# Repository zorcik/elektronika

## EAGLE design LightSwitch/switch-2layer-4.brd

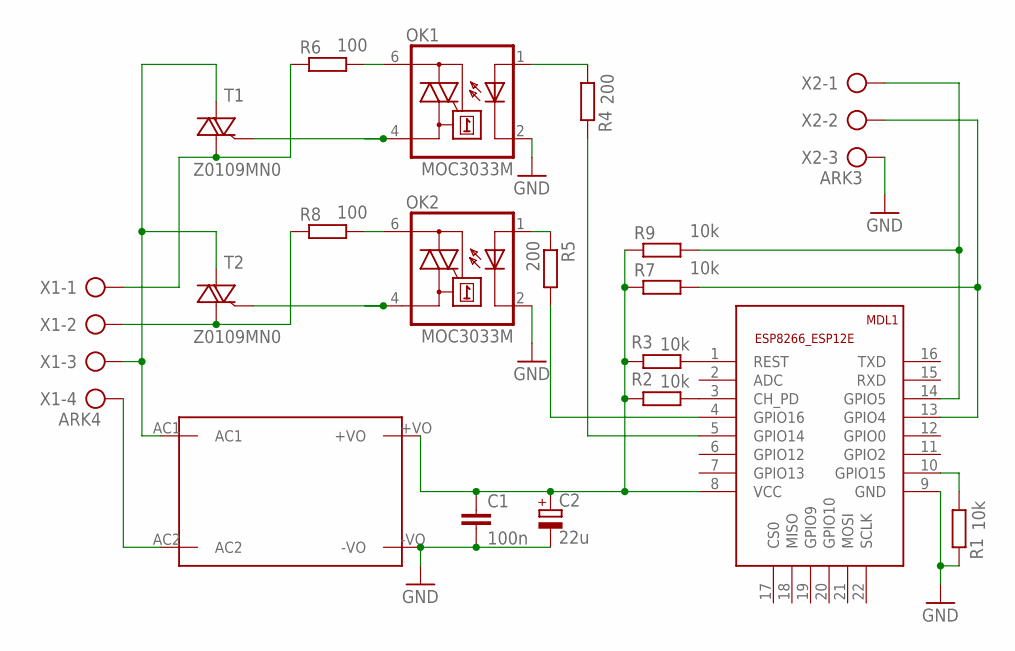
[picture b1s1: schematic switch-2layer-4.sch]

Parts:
C1: 100n; C1206
C2: 22u; E2,5-6
MDL1: ESP12-F; ESP8266-ESP12E
OK1, OK2: MOC3033M; DIL06
R1, R2, R3, R7, R9: 10k; R1206
R4, R5: 200; R1206
R6, R8: 100; R1206
T1, T2: Z0109MN0; SOT223
U$1: HLK-PM03
X1: ARK4; AK500/4
X2: ARK3; AK500/3

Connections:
GND: C1.2, C2.-, MDL1.9 (GND), OK1.2 (C), OK2.2 (C), R1.2, U$1.-VO, X2.3
unnamed: MDL1.10 (GPIO15), R1.1
unnamed: MDL1.1 (REST), R3.1
unnamed: MDL1.3 (CH_PD), R2.1
unnamed: C1.1, C2.+, MDL1.8 (VCC), R2.2, R3.2, R7.1, R9.1, U$1.+VO
unnamed: OK1.6 (A2), R6.2
unnamed: OK2.6 (A2), R8.2
unnamed: OK2.1 (A), R5.1
unnamed: OK1.1 (A), R4.1
unnamed: MDL1.4 (GPIO16), R5.2
unnamed: MDL1.5 (GPIO14), R4.2
unnamed: OK1.4 (A1), T1.3 (G)
unnamed: R8.1, T2.2 (CM), T2.4 (CM), X1.2
unnamed: OK2.4 (A1), T2.3 (G)
unnamed: U$1.AC2, X1.4
unnamed: T1.1 (LD), T2.1 (LD), U$1.AC1, X1.3
unnamed: MDL1.14 (GPIO5), R9.2, X2.1
unnamed: MDL1.13 (GPIO4), R7.2, X2.2
unnamed: R6.1, T1.2 (CM), T1.4 (CM), X1.1

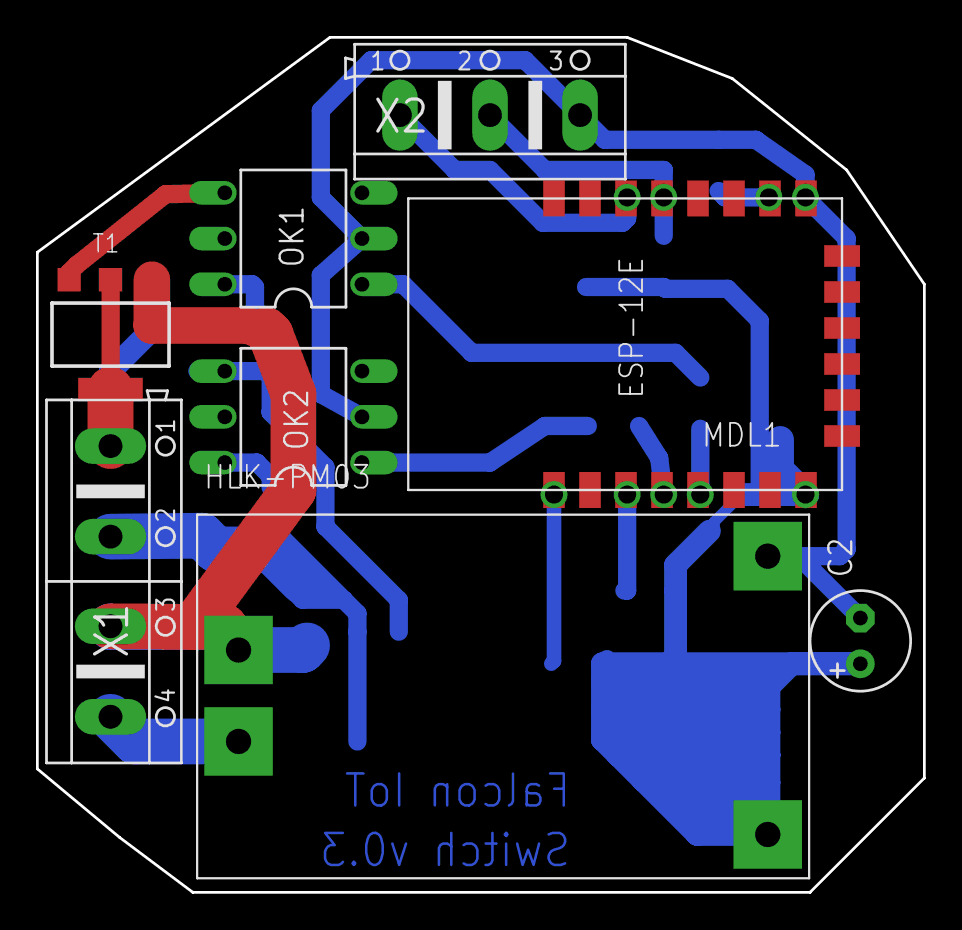
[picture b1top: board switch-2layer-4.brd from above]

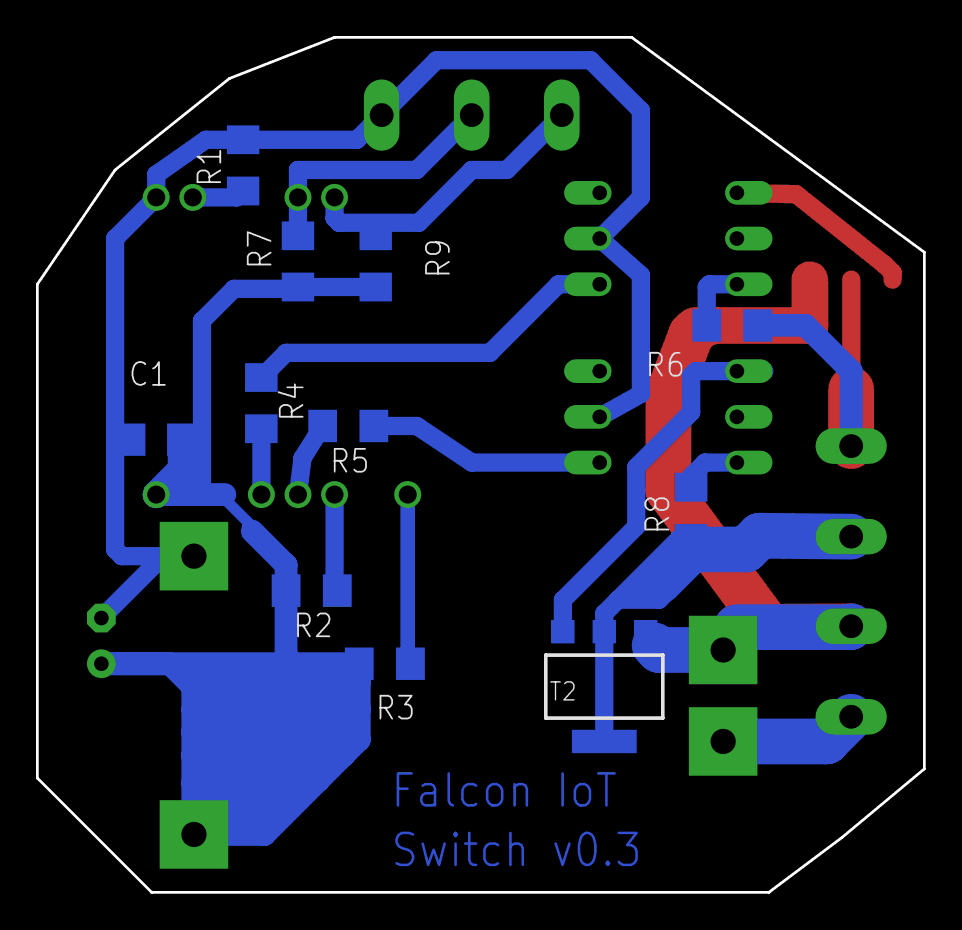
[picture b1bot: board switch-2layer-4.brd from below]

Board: 2 copper layers, 49.3 x 47.5 mm, 19 parts (11 on the bottom side), 19 nets.

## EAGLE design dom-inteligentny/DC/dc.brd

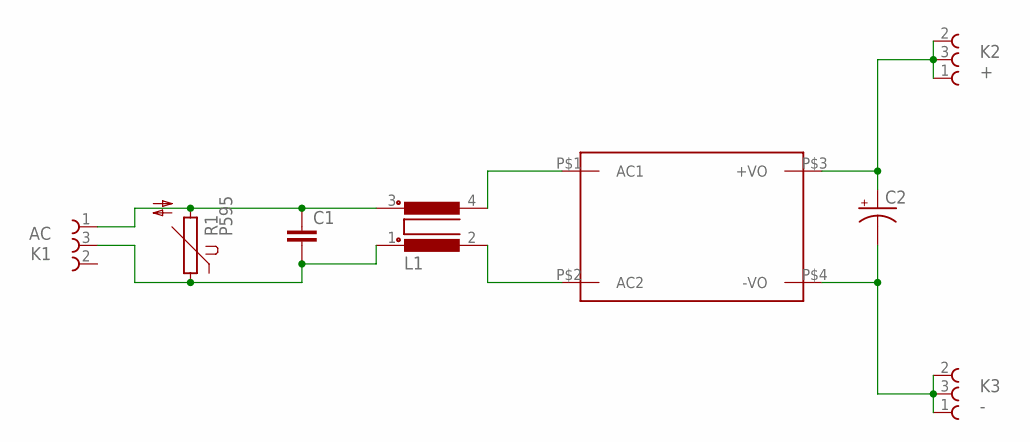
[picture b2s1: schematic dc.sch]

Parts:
C1: C15/7; C15B7
C2: CPOL-USE10-20; EB20D
K1: AC; 691218410003
K2: +; 691218410003
K3: -; 691218410003
L1: R1003UB5; B5
R1: P595
U$1: HLK-PM03HLK-20M; HLK-20M

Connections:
unnamed: C1.1, K1.1 (3), L1.3, R1.2
unnamed: L1.4, U$1.P$1 (AC1)
unnamed: L1.2, U$1.P$2 (AC2)
unnamed: C1.2, K1.3 (2), L1.1, R1.1
unnamed: C2.+, K2.1 (3), K2.2 (1), K2.3 (2), U$1.P$3 (+VO)
unnamed: C2.-, K3.1 (3), K3.2 (1), K3.3 (2), U$1.P$4 (-VO)

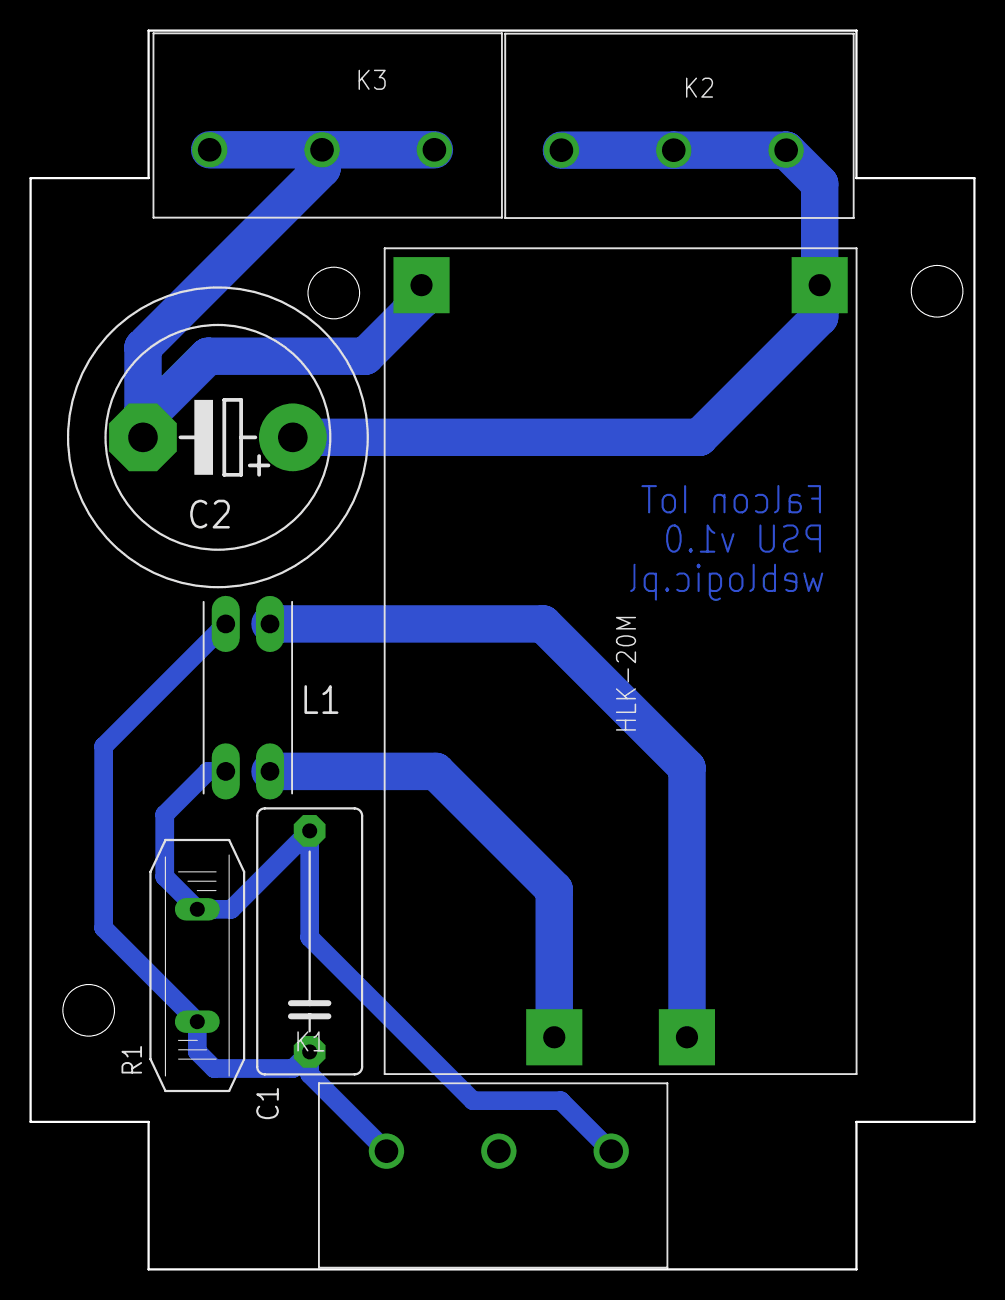
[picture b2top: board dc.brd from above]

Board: 2 copper layers, 64.0 x 84.0 mm, 8 parts (0 on the bottom side), 6 nets.

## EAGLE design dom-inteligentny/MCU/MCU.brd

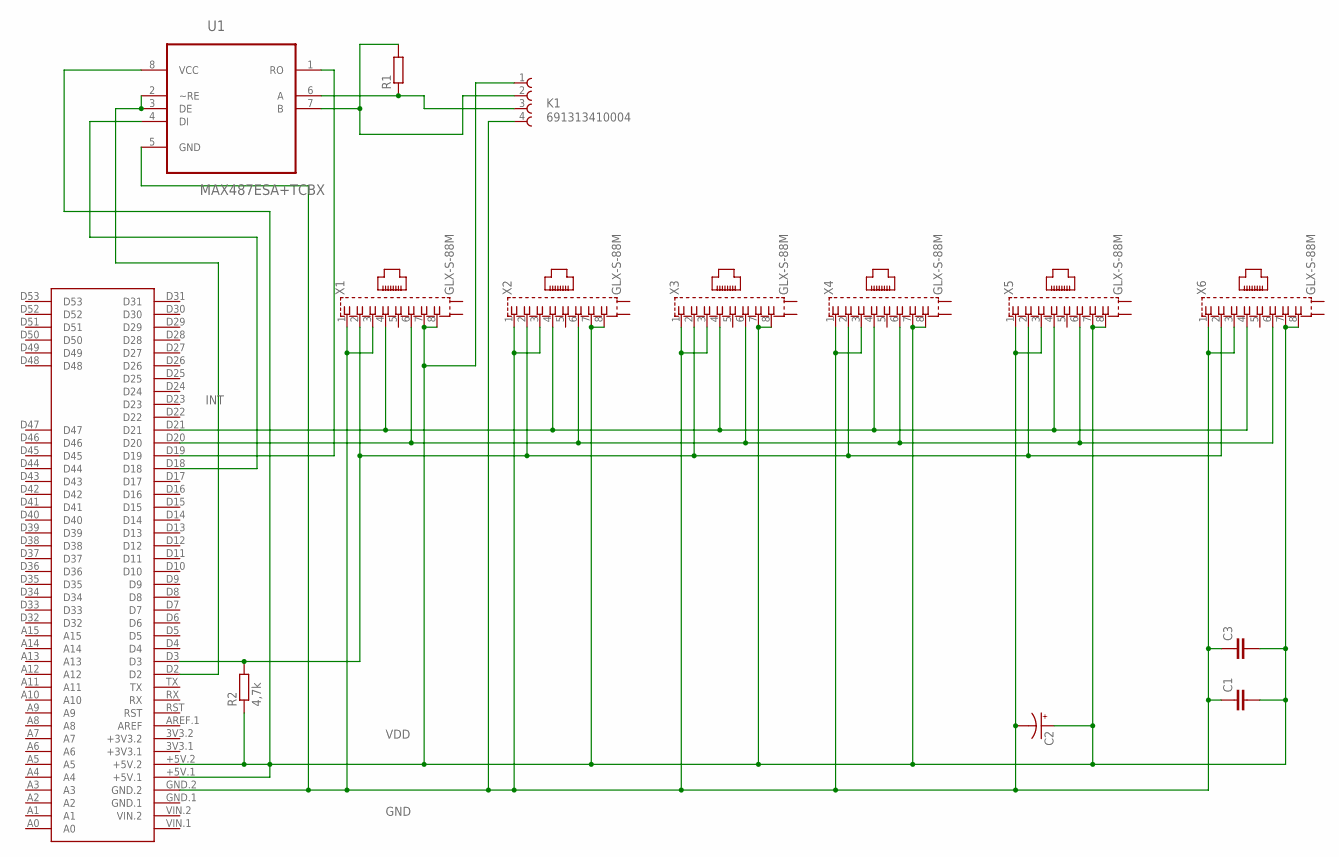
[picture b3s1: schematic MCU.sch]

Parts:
C1, C3: CC1206; C1206
C2: CPOL-US153CLV-0807; 153CLV-0807
K1: 691313410004
R1: RR1206; R1206
R2: 4,7k; R1206
U1: MAX487ESA+TCBX; SOIC127P600X175-8N
U$1: MEGA2560_MIKRO
X1, X2, X3, X4, X5, X6: GLX-S-88M

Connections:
GND: C1.1, C2.-, C3.1, K1.4, U1.5 (GND), U$1.GND.2, X1.1, X1.3, X2.1, X2.3, X3.1, X3.3, X4.1, X4.3, X5.1, X5.3, X6.1, X6.3
INT: R2.2, U$1.D3, X1.2, X2.2, X3.2, X4.2, X5.2, X6.2
unnamed: U1.4 (DI), U$1.D18
unnamed: U1.1 (RO), U$1.D19
unnamed: U1.2 (~RE), U1.3 (DE), U$1.D2
unnamed: K1.3, R1.1, U1.6 (A)
unnamed: K1.2, R1.2, U1.7 (B)
unnamed: U$1.D20, X1.6, X2.6, X3.6, X4.6, X5.6, X6.6
unnamed: U$1.D21, X1.4, X2.4, X3.4, X4.4, X5.4, X6.4
VDD: C1.2, C2.+, C3.2, K1.1, R2.1, U1.8 (VCC), U$1.+5V.1, U$1.+5V.2, X1.7, X1.8, X2.7, X2.8, X3.7, X3.8, X4.7, X4.8, X5.7, X5.8, X6.7, X6.8

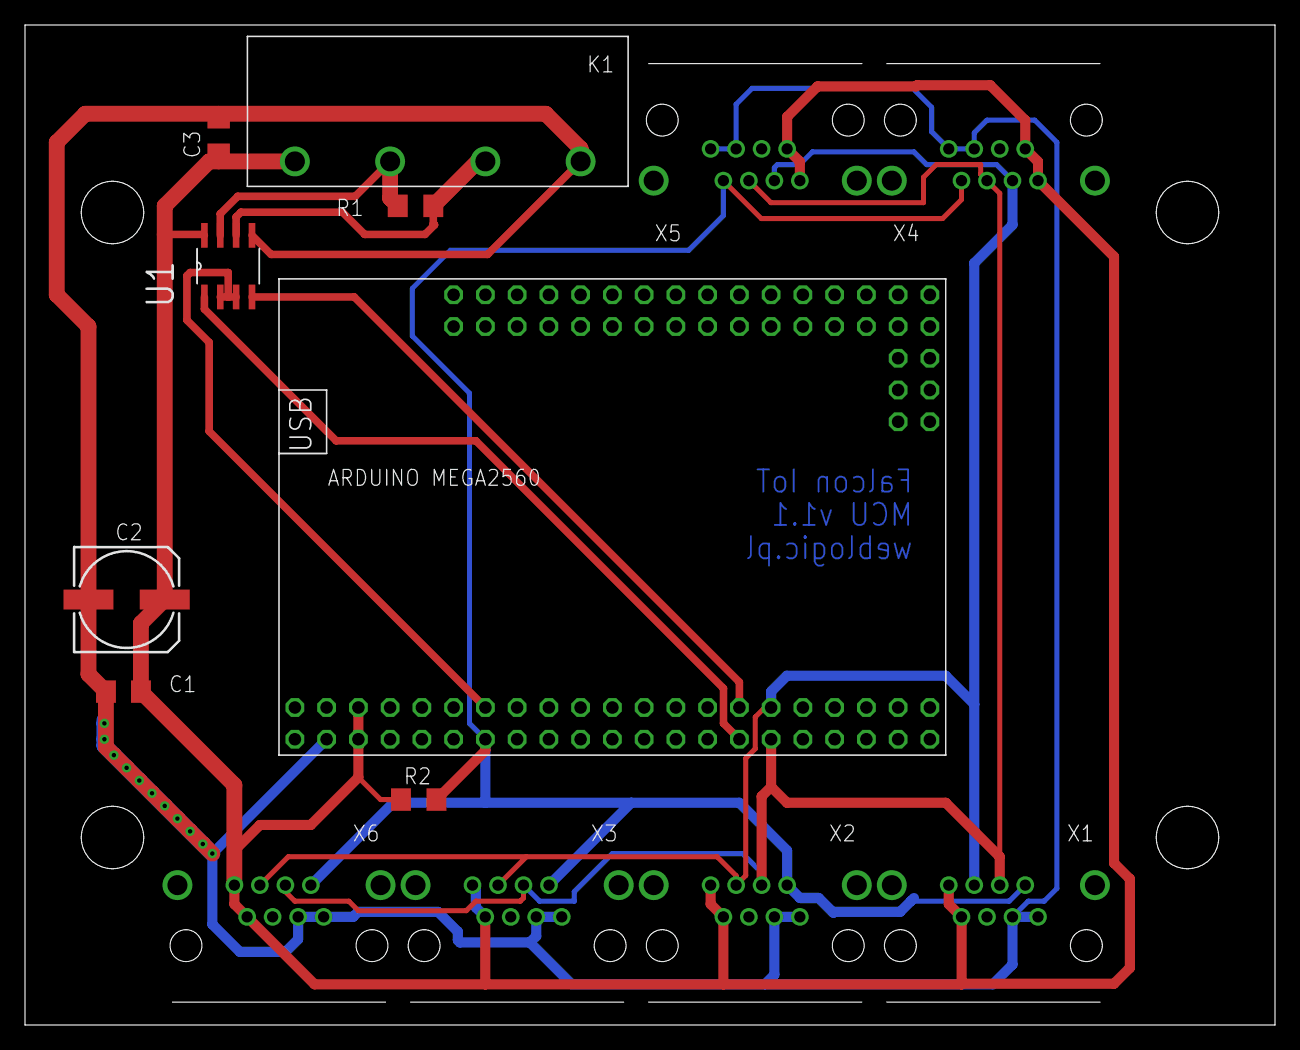
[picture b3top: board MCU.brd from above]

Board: 2 copper layers, 100.0 x 80.0 mm, 14 parts (0 on the bottom side), 10 nets.

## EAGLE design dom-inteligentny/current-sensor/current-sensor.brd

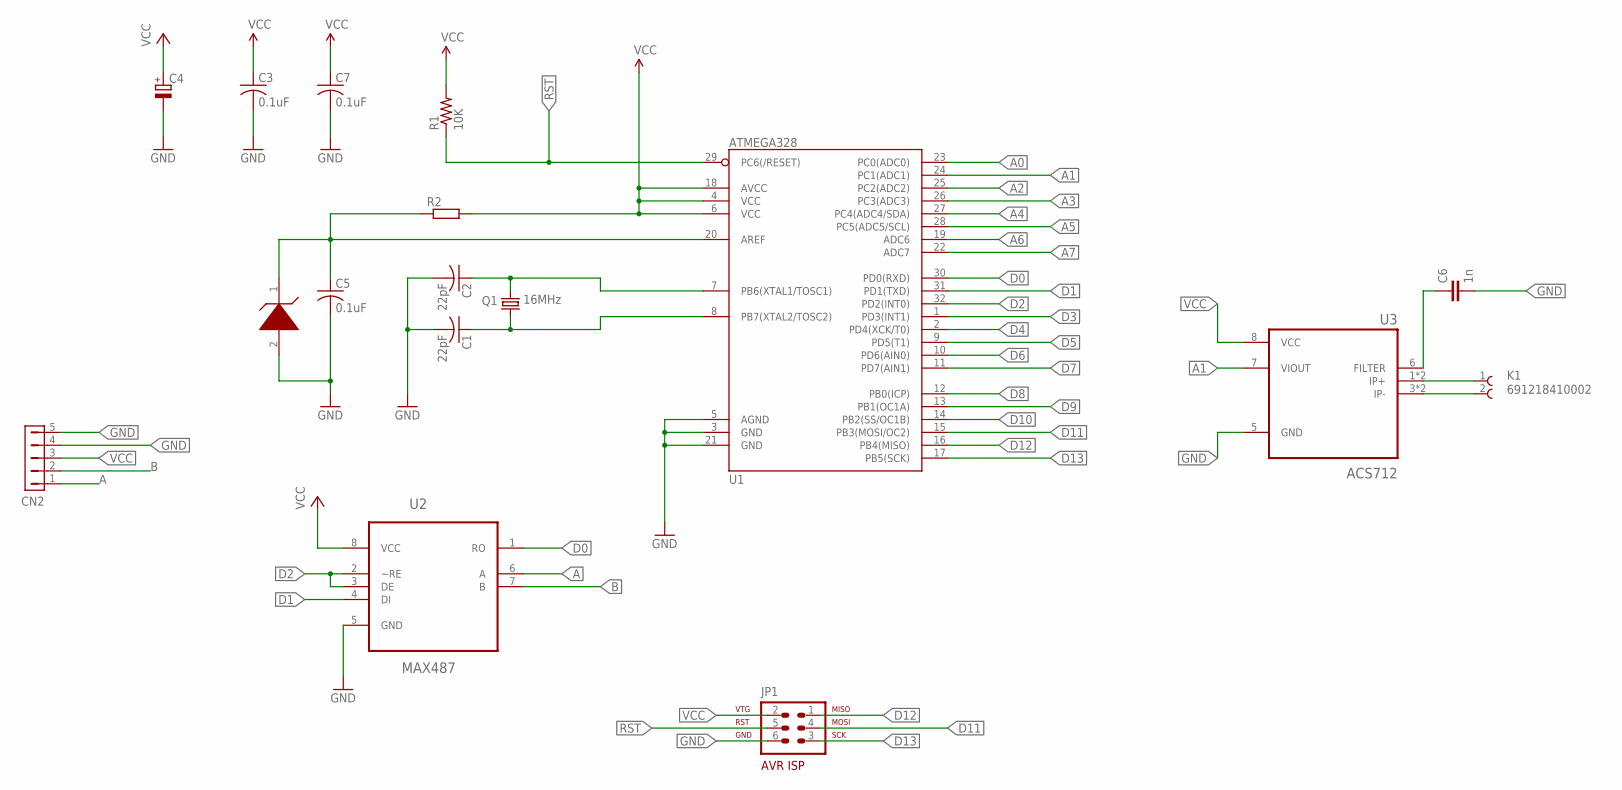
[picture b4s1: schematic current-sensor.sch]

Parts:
C1, C2: 22pF; C1206
C3, C5, C7: 0.1uF; C0805
C4: CPOL-EUSANYO_SMD_C6; SANYO-OSCON_SMD_C6
C6: 1n; C1206
CN2: HDR-1X5-SIP-100; SIP-100-5V
JP1: AVR-ISP-6
K1: 691218410002
Q1: 16MHz; HC49/S
R1: 10K; R1206
R2: RR1206; R1206
U1: ATMEGA328; TQFP32-08
U2: MAX487; SOIC127P600X175-8N
U3: ACS712; SOIC127P600X175-8N
U$1: LM4040; SOT23

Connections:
A: CN2.1, U2.6 (A)
A0: U1.23 (PC0(ADC0))
A1: U1.24 (PC1(ADC1)), U3.7 (VIOUT)
A2: U1.25 (PC2(ADC2))
A3: U1.26 (PC3(ADC3))
A4: U1.27 (PC4(ADC4/SDA))
A5: U1.28 (PC5(ADC5/SCL))
A6: U1.19 (ADC6)
A7: U1.22 (ADC7)
AREF: C5.1, R2.1, U1.20 (AREF), U$1.1 (CATHODE)
B: CN2.2, U2.7 (B)
D0: U1.30 (PD0(RXD)), U2.1 (RO)
D1: U1.31 (PD1(TXD)), U2.4 (DI)
D2: U1.32 (PD2(INT0)), U2.2 (~RE), U2.3 (DE)
D3: U1.1 (PD3(INT1))
D4: U1.2 (PD4(XCK/T0))
D5: U1.9 (PD5(T1))
D6: U1.10 (PD6(AIN0))
D7: U1.11 (PD7(AIN1))
D8: U1.12 (PB0(ICP))
D9: U1.13 (PB1(OC1A))
D10: U1.14 (PB2(SS/OC1B))
D11: JP1.4, U1.15 (PB3(MOSI/OC2))
D12: JP1.1, U1.16 (PB4(MISO))
D13: JP1.3, U1.17 (PB5(SCK))
GND: C1.2, C2.2, C3.2, C4.-, C5.2, C6.2, C7.2, CN2.4, CN2.5, JP1.6, U1.3 (GND), U1.5 (AGND), U1.21 (GND), U2.5 (GND), U3.5 (GND), U$1.2 (ANODE)
unnamed: K1.1, U3.1 (IP+), U3.2 (IP+)
unnamed: K1.2, U3.3 (IP-), U3.4 (IP-)
unnamed: C6.1, U3.6 (FILTER)
unnamed: C2.1, Q1.2, U1.7 (PB6(XTAL1/TOSC1))
unnamed: C1.1, Q1.1, U1.8 (PB7(XTAL2/TOSC2))
RST: JP1.5, R1.1, U1.29 (PC6(/RESET))
VCC: C3.1, C4.+, C7.1, CN2.3, JP1.2, R1.2, R2.2, U1.4 (VCC), U1.6 (VCC), U1.18 (AVCC), U2.8 (VCC), U3.8 (VCC)

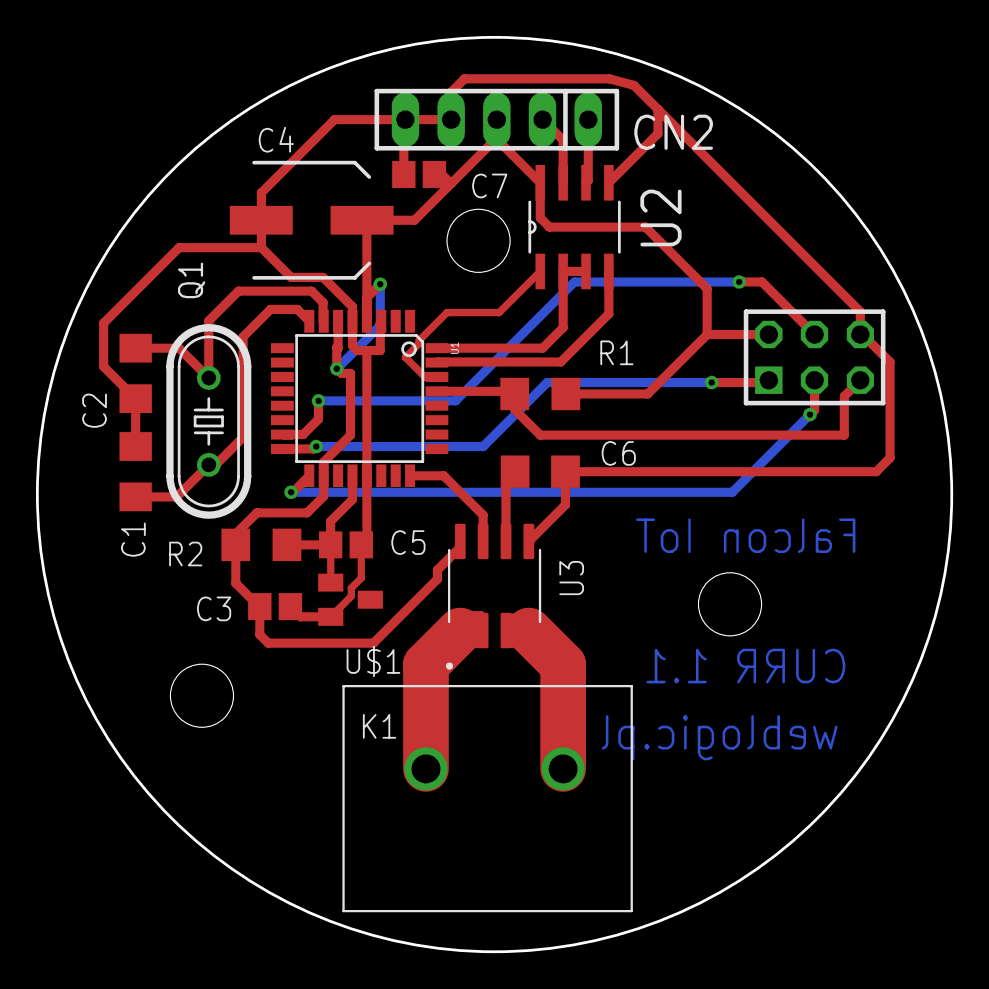
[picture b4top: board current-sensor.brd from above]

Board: 2 copper layers, 50.8 x 50.8 mm, 17 parts (0 on the bottom side), 18 nets.

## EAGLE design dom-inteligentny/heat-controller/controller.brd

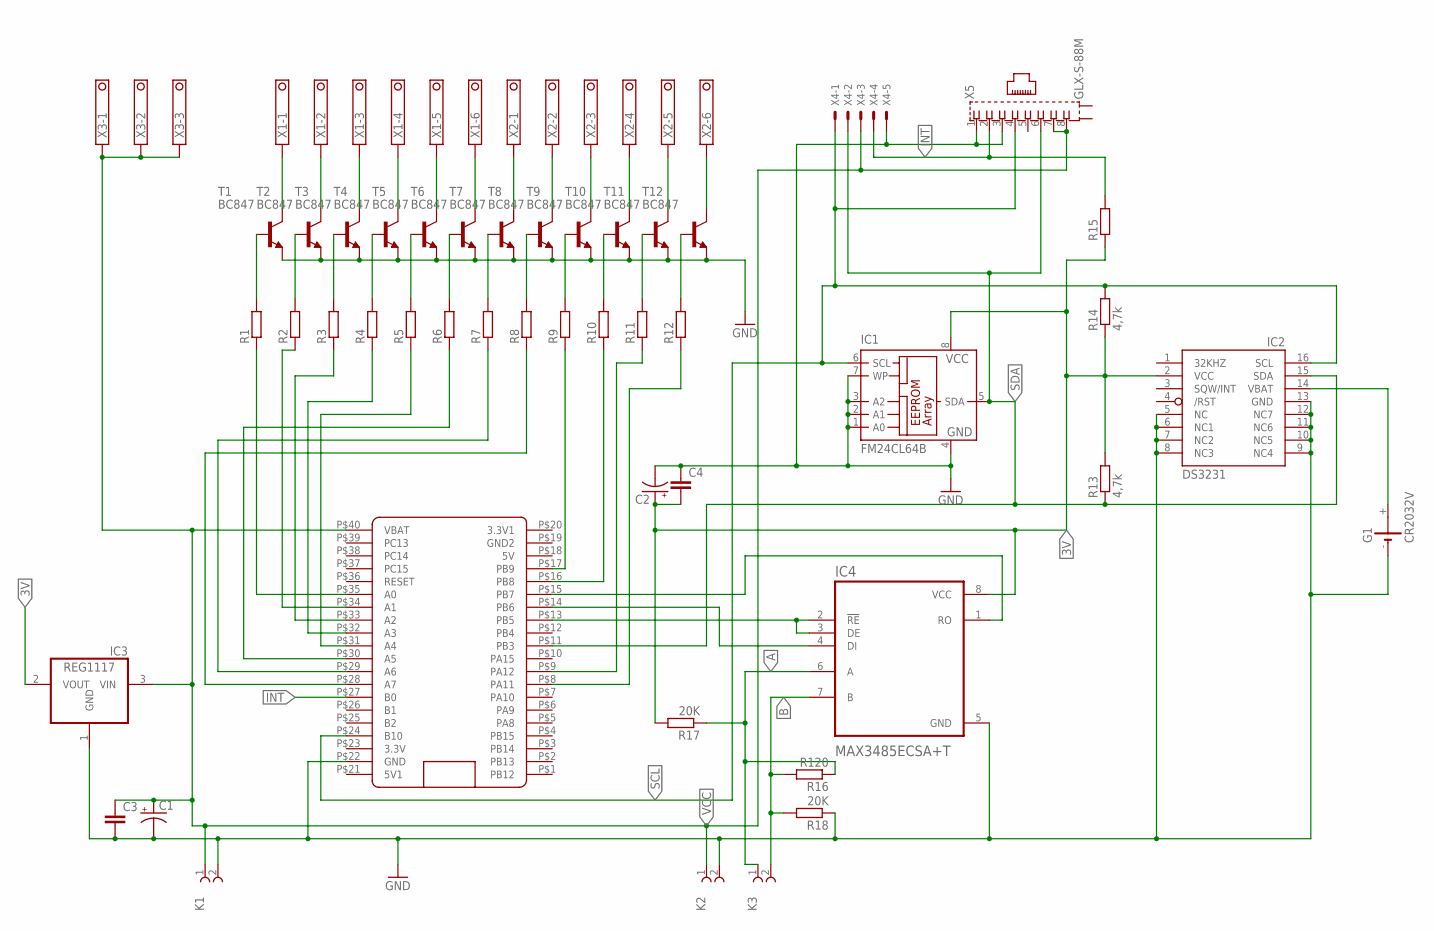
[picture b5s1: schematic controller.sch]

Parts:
C1, C2: CPOL-US153CLV-0810; 153CLV-0810
C3, C4: C; C0805
G1: CR2032V
IC1: FM24CL64B; SO-08M
IC2: DS3231; SO16W
IC3: REG1117; SOT223
IC4: MAX3485ECSA+T; SOIC127P600X175-8N
K1, K2, K3: 691218410002
R1, R2, R3, R4, R5, R6, R7, R8, R9, R10, R11, R12, R15: RR1206; R1206
R13, R14: 4,7k; R1206
R16: R120; R1206
R17, R18: 20K; R1206
T1, T2, T3, T4, T5, T6, T7, T8, T9, T10, T11, T12: BC847; SOT23
U$1: BLACK_STM32F411; BLACK_PILL
X1, X2: TERMINAL-BLOCK-3.5MM-6-PIN-LONG-PAD; TERMINAL-BLOCK-6-PIN-3.5MM-LONG-PAD
X3: TERMINAL-BLOCK-3.5MM-3-PIN-LONG-PAD; TERMINAL-BLOCK-3-PIN-3.5MM-LONG-PAD
X4: JST-XH-05-PIN-LONG-PAD; JST-XH-05-PACKAGE-LONG-PAD
X5: GLX-S-88M

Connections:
3V: C2.+, C4.2, IC1.8 (VCC), IC2.2 (VCC), IC3.2 (VOUT), IC4.8 (VCC), R13.2, R14.1, R15.1, R17.2
5V1: U$1.P$21 (5V1)
A: IC4.6 (A), K3.1, R16.1, R17.1
B: IC4.7 (B), K3.2, R16.2, R18.2
GND: C1.-, C2.-, C3.2, C4.1, G1.-, IC1.1 (A0), IC1.2 (A1), IC1.3 (A2), IC1.4 (GND), IC1.7 (WP), IC2.5 (NC), IC2.6 (NC1), IC2.7 (NC2), IC2.8 (NC3), IC2.9 (NC4), IC2.10 (NC5), IC2.11 (NC6), IC2.12 (NC7), IC2.13 (GND), IC3.1 (GND), IC4.5 (GND), K1.2, K2.2, R18.1, T1.2 (E), T2.2 (E), T3.2 (E), T4.2 (E), T5.2 (E), T6.2 (E), T7.2 (E), T8.2 (E), T9.2 (E), T10.2 (E), T11.2 (E), T12.2 (E), U$1.P$22 (GND), X4.5, X5.1, X5.3
INT: R15.2, U$1.P$27 (B0), X4.4, X5.2
unnamed: G1.+, IC2.14 (VBAT)
unnamed: IC4.2 (!RE), IC4.3 (DE), U$1.P$13 (PB5)
unnamed: IC4.4 (DI), U$1.P$14 (PB6)
unnamed: IC4.1 (RO), U$1.P$15 (PB7)
unnamed: R1.1, U$1.P$35 (A0)
unnamed: R2.1, U$1.P$34 (A1)
unnamed: R3.1, U$1.P$33 (A2)
unnamed: R4.1, U$1.P$32 (A3)
unnamed: R5.1, U$1.P$31 (A4)
unnamed: R6.1, U$1.P$30 (A5)
unnamed: R7.1, U$1.P$29 (A6)
unnamed: R8.1, U$1.P$28 (A7)
unnamed: R9.1, U$1.P$17 (PB9)
unnamed: R10.1, U$1.P$16 (PB8)
unnamed: R11.1, U$1.P$9 (PA12)
unnamed: R12.1, U$1.P$8 (PA11)
unnamed: R1.2, T1.1 (B)
unnamed: R2.2, T2.1 (B)
unnamed: R3.2, T3.1 (B)
unnamed: R4.2, T4.1 (B)
unnamed: R5.2, T5.1 (B)
unnamed: R6.2, T6.1 (B)
unnamed: R7.2, T7.1 (B)
unnamed: R8.2, T8.1 (B)
unnamed: R9.2, T9.1 (B)
unnamed: R10.2, T10.1 (B)
unnamed: R11.2, T11.1 (B)
unnamed: R12.2, T12.1 (B)
unnamed: T1.3 (C), X1.1
unnamed: T2.3 (C), X1.2
unnamed: T3.3 (C), X1.3
unnamed: T4.3 (C), X1.4
unnamed: T5.3 (C), X1.5
unnamed: T6.3 (C), X1.6
unnamed: T7.3 (C), X2.1
unnamed: T8.3 (C), X2.2
unnamed: T9.3 (C), X2.3
unnamed: T10.3 (C), X2.4
unnamed: T11.3 (C), X2.5
unnamed: T12.3 (C), X2.6
SCL: IC1.6 (SCL), IC2.16 (SCL), R14.2, U$1.P$24 (B10), X4.1, X5.4
SDA: IC1.5 (SDA), IC2.15 (SDA), R13.1, U$1.P$11 (PB3), X4.2, X5.6
VCC: C1.+, C3.1, IC3.3 (VIN), K1.1, K2.1, U$1.P$40 (VBAT), X3.1, X3.2, X3.3, X4.3, X5.7, X5.8

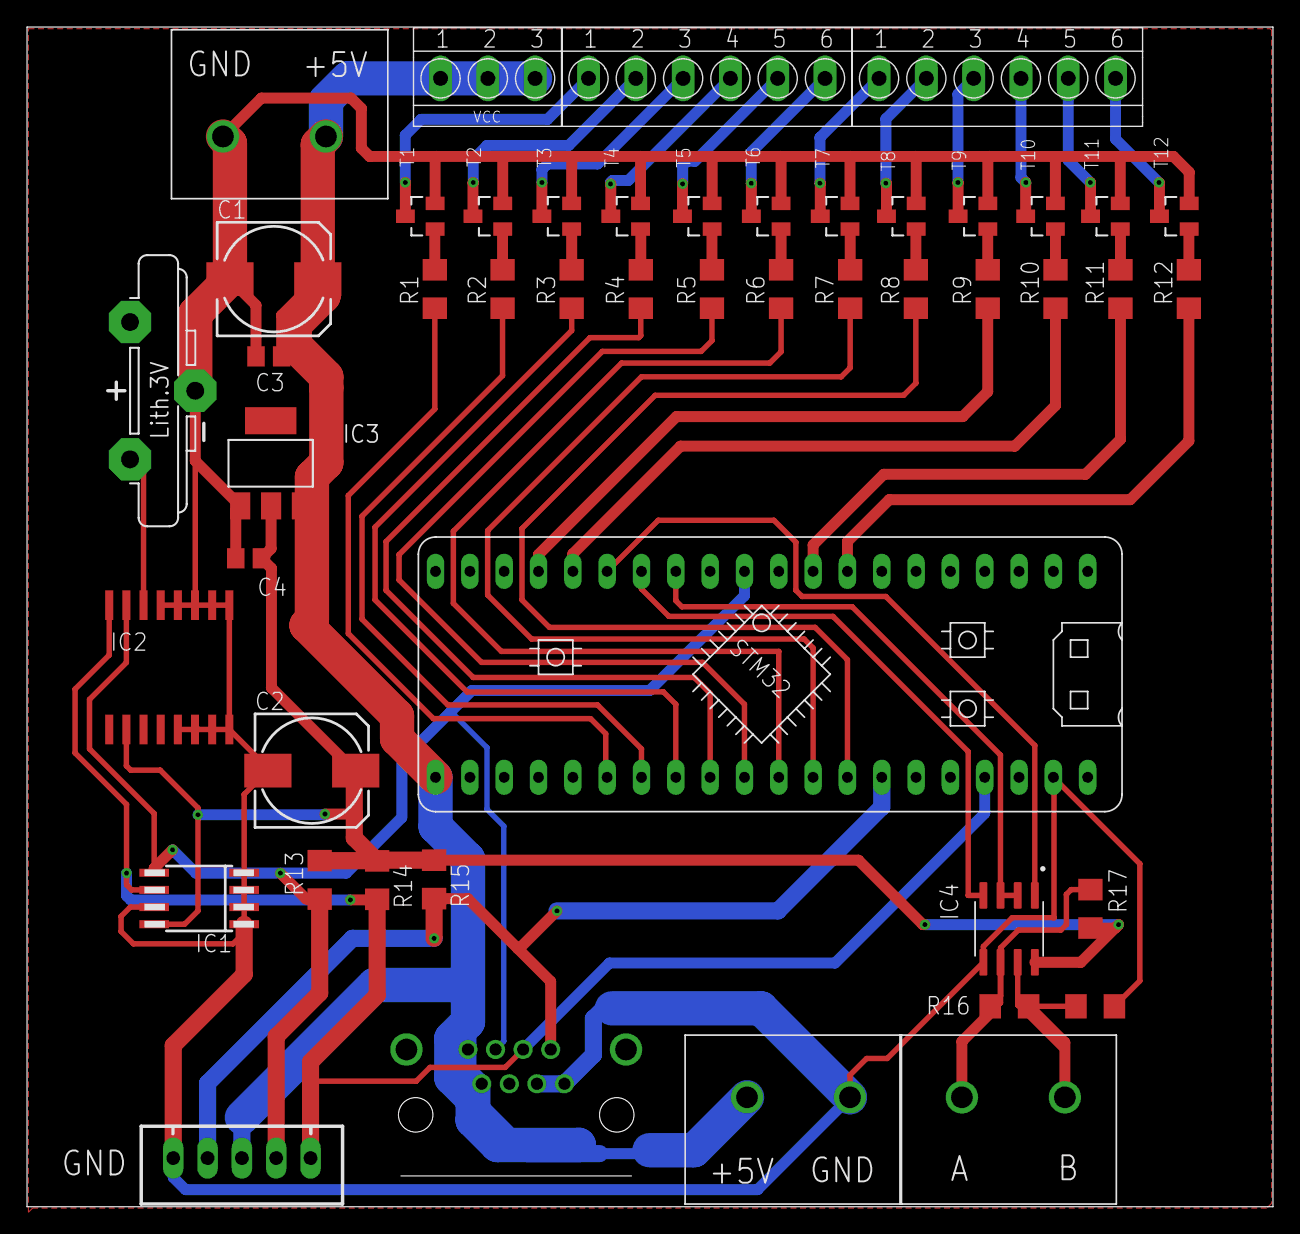
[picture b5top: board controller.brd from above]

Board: 2 copper layers, 92.2 x 87.3 mm, 48 parts (0 on the bottom side), 48 nets.

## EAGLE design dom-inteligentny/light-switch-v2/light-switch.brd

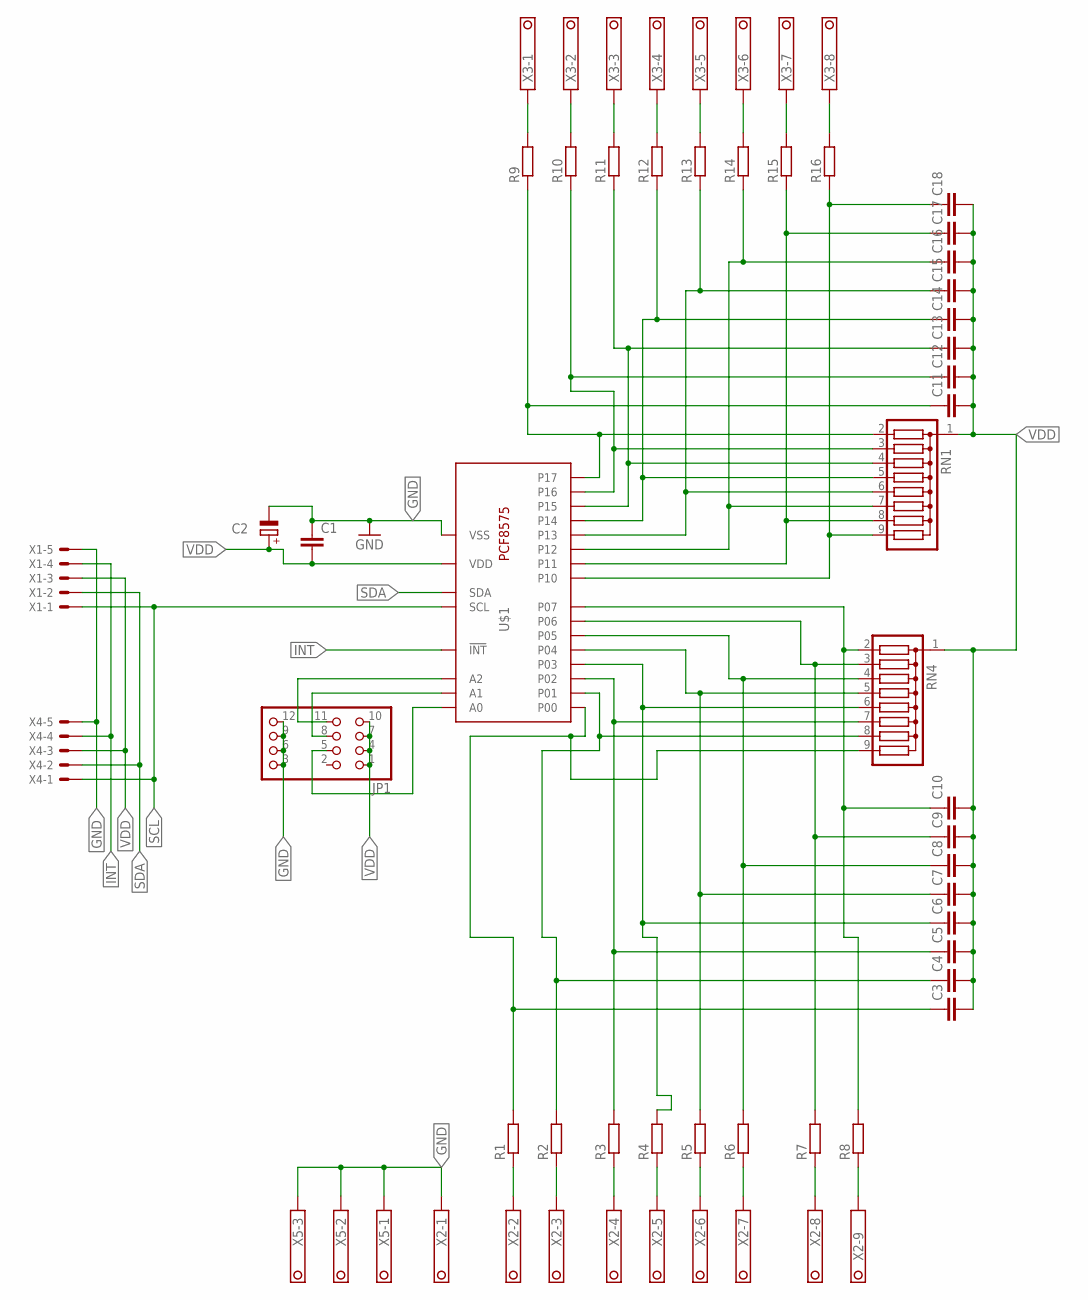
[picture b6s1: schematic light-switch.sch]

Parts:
C1: CC1206; C1206
C2: CPOL-EU150CLZ-0810; 150CLZ-0810
C3, C4, C5, C6, C7, C8, C9, C10, C11, C12, C13, C14, C15, C16, C17, C18: C; C0805
JP1: PINHD-3X4; 3X04
R1, R2, R3, R4, R5, R6, R7, R8, R9, R10, R11, R12, R13, R14, R15, R16: RR1206; R1206
RN1, RN4: G08R; SIL9
U$1: PCF8575CSSOP24; SOP65P775X200-24N
X1, X4: JST-XH-05-PIN-LONG-PAD; JST-XH-05-PACKAGE-LONG-PAD
X2: TERMINAL-BLOCK-3.5MM-9-PIN-LONG-PAD; TERMINAL-BLOCK-9-PIN-3.5MM-LONG-PAD
X3: TERMINAL-BLOCK-3.5MM-8-PIN-LONG-PAD; TERMINAL-BLOCK-8-PIN-3.5MM-LONG-PAD
X5: TERMINAL-BLOCK-3.5MM-3-PIN-LONG-PAD; TERMINAL-BLOCK-3-PIN-3.5MM-LONG-PAD

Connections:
GND: C1.1, C2.-, JP1.3, JP1.6, JP1.9, JP1.12, U$1.12 (VSS), X1.5, X2.1, X4.5, X5.1, X5.2, X5.3
INT: U$1.1 (!INT), X1.4, X4.4
unnamed: C11.1, R9.1, RN1.2, U$1.20 (P17)
unnamed: R8.1, X2.9
unnamed: C12.1, R10.1, RN1.3, U$1.19 (P16)
unnamed: C13.1, R11.1, RN1.4, U$1.18 (P15)
unnamed: C14.1, R12.1, RN1.5, U$1.17 (P14)
unnamed: C15.1, R13.1, RN1.6, U$1.16 (P13)
unnamed: C16.1, R14.1, RN1.7, U$1.15 (P12)
unnamed: C17.1, R15.1, RN1.8, U$1.14 (P11)
unnamed: C18.1, R16.1, RN1.9, U$1.13 (P10)
unnamed: C3.1, R1.2, RN4.9, U$1.4 (P00)
unnamed: C4.1, R2.2, RN4.8, U$1.5 (P01)
unnamed: C5.1, R3.2, RN4.7, U$1.6 (P02)
unnamed: C6.1, R4.2, RN4.6, U$1.7 (P03)
unnamed: C7.1, R5.2, RN4.5, U$1.8 (P04)
unnamed: C8.1, R6.2, RN4.4, U$1.9 (P05)
unnamed: C9.1, R7.2, RN4.3, U$1.10 (P06)
unnamed: C10.1, R8.2, RN4.2, U$1.11 (P07)
unnamed: R1.1, X2.2
unnamed: JP1.11, U$1.3 (A2)
unnamed: JP1.8, U$1.2 (A1)
unnamed: JP1.5, U$1.21 (A0)
unnamed: R2.1, X2.3
unnamed: R3.1, X2.4
unnamed: R4.1, X2.5
unnamed: R5.1, X2.6
unnamed: R6.1, X2.7
unnamed: R7.1, X2.8
unnamed: R9.2, X3.1
unnamed: R10.2, X3.2
unnamed: R11.2, X3.3
unnamed: R12.2, X3.4
unnamed: R13.2, X3.5
unnamed: R14.2, X3.6
unnamed: R15.2, X3.7
unnamed: R16.2, X3.8
SCL: U$1.22 (SCL), X1.1, X4.1
SDA: U$1.23 (SDA), X1.2, X4.2
VDD: C1.2, C2.+, C3.2, C4.2, C5.2, C6.2, C7.2, C8.2, C9.2, C10.2, C11.2, C12.2, C13.2, C14.2, C15.2, C16.2, C17.2, C18.2, JP1.1, JP1.4, JP1.7, JP1.10, RN1.1, RN4.1, U$1.24 (VDD), X1.3, X4.3

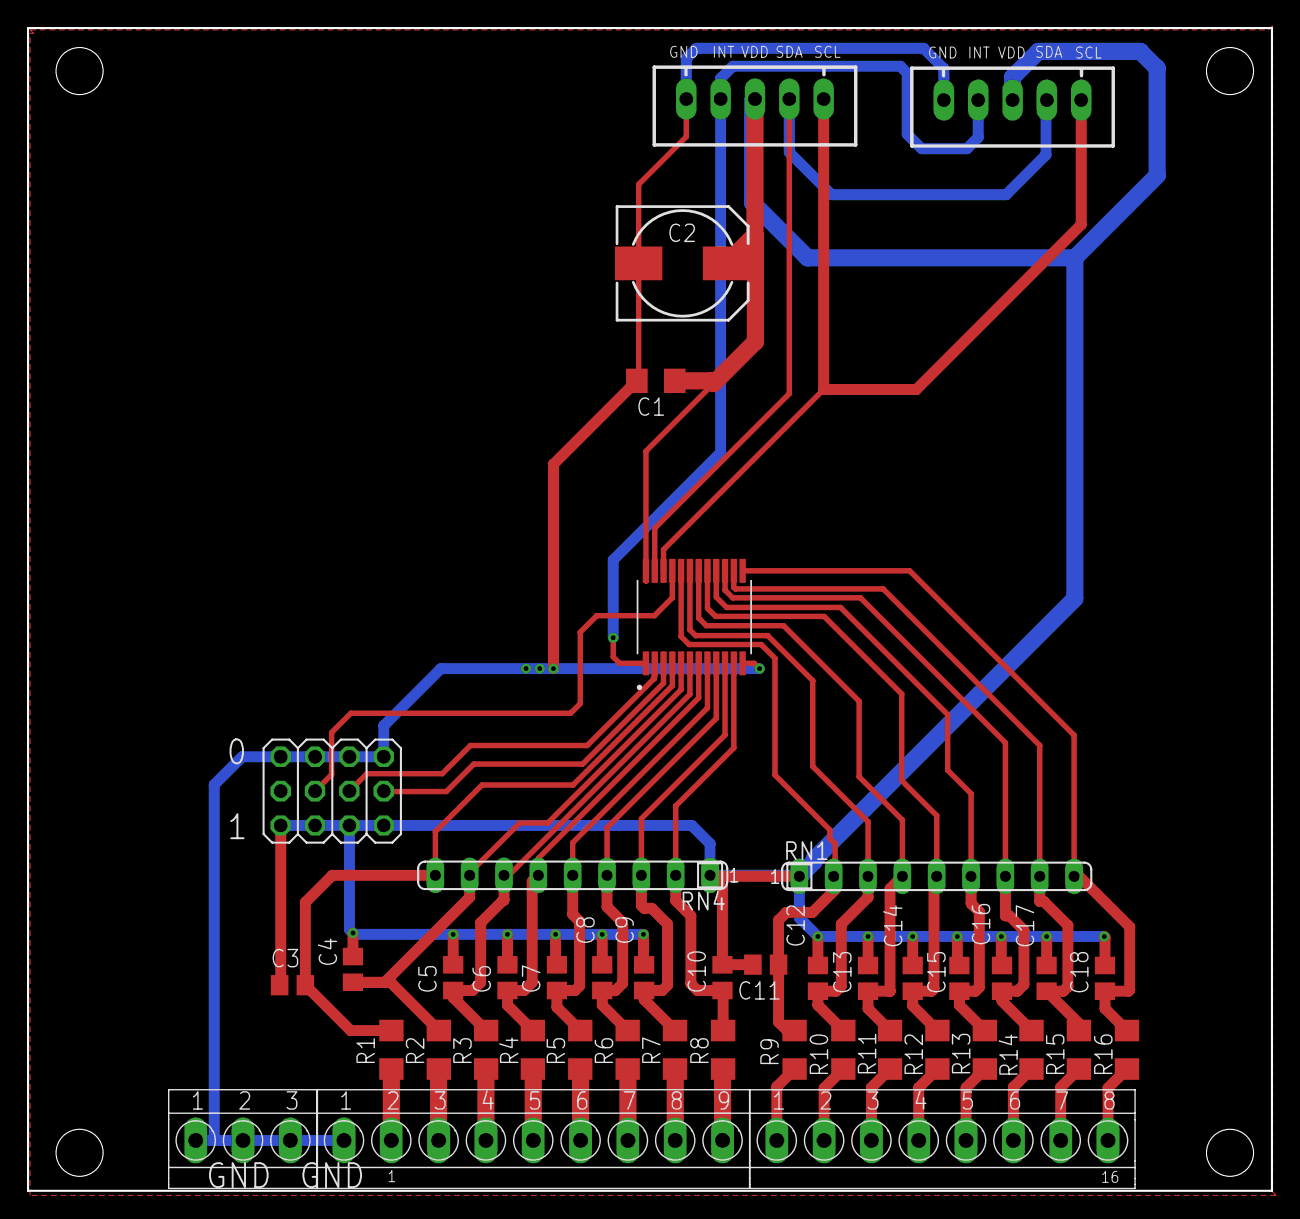
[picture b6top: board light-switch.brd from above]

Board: 2 copper layers, 92.0 x 86.0 mm, 43 parts (0 on the bottom side), 40 nets.

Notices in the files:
parts and their libraries:
Wurth_Elektronik_Electromechanic_Termina: Copyright: Würth Elektronik
con-hdrs40: Copyright (C) 2004, Bob Starr (bobstarr@mindspring.com)
SparkFun: Licensing: CC v3.0 Share-Alike You are welcome to use this library for commercial purposes.
